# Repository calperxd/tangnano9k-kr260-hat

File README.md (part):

# Tang Nano 9K Custom HAT for AMD Kria KR260

Hardware, firmware, integration and validation requirements for a custom FPGA board based on the Tang Nano 9K, installed directly on the 40-pin J21 header of the KR260.

| Top | Bottom |
|:---:|:---:|
|  |  |

<p align="center"><sub>KiCad 3D renders of board revision 0.4 (65 × 56.5 mm, 4 layers). The board has not been manufactured yet.</sub></p>

| Field | Value |
|---|---|
| Document revision | 0.7 — TMI7003C checked against its datasheet; its LCSC number in the BOM |
| Date | 2026-10-21 |
| Previous revisions | 0.6 — power from the USB-C or from the KR260 J21 5 V (Schottky OR-ing); 0.5 — English translation, KR260 schematic cross-check, PCB prepared for JLCPCB; 0.4 — preliminary schematic and proposed parts; 0.3 — integration with the KR260; 0.2 — consolidation of the HAT scope (all dated 2026-10-21) |
| Host platform | AMD Kria KR260; K26 SOM with XCK26-SFVC784-2LV-C/I (F10) |
| KR260 environment | KAKUEI-OS (customized PetaLinux 2024.2), Vivado/Vitis 2024.2, PL with DPU (DPUCZDX8G) and VCU, applications in Docker containers (R4) |
| Status | Specification with a preliminary schematic and a PCB prepared for JLCPCB fabrication and assembly in KiCad 10 (`hardware/`, Proposed); production files generated for an order, not released; mechanical fit with the KR260 checked against its 3D model (XTP744, F14), with the physical fit check still **Pending**; pinout, outline and PCB still subject to development and validation |
| Planned CAD | KiCad 10 |
| Expansion board FPGA | Gowin GW1NR-LV9QN88PC6/I5, QN88P package |

> **This document is not a release for manufacturing.** The number of usable signals on J21, the clock pins, the voltages, the mechanical fit and the link timing need to be proven in the design. **16 bits at 50 MHz correspond to 100 MB/s raw by calculation, not to a rate already measured or guaranteed.**
>
> **Revision 0.3:** the J21 → K26 map comes from a secondary source and is **preliminary — confirm in XTP743**. The signal allocation on J21 is **Proposed**. Nothing in this revision was measured or validated in hardware.
>
> **Revision 0.4:** the preliminary schematic in `hardware/` was captured in KiCad 10. An ERC with no violations and a netlist checked against the intended connections are document checks, not electrical validation. The new parts are **Proposed** (section 16.1). After the capture, the five sheets were redrawn with wires, power symbols and labels, with no change in connectivity (section 17.1). There is also a PCB study with a provisional outline and automatic routing (section 17.2), which neither defines the mechanics nor is a release for manufacturing.
>
> **Revision 0.5:** the document was translated to English. The J21 → K26 map was cross-checked against the KR260 carrier schematic (cited as XTP743; F12) and the K26 SOM XDC (F13): the 28 signal contacts match with 0 differences, the section 6.4 items are answered except PUDC_B (ISO-14, still **Pending**), and the rails behind the J21 3.3 V and the bank 43/44 VCCO are identified (ISO-10); these are document cross-checks, not hardware validation. The PCB was prepared for JLCPCB fabrication and assembly (section 17.2): English KiCad texts and silkscreen with J21 pin labels, JLCPCB design rules and stackup (Proposed), and the USB pair rerouted on F.Cu without vias (in rev. 0.4: D+ on F.Cu and D− on In2.Cu with 3 vias, 16.0/20.0 mm); other rev. 0.4 values that changed are given next to the new ones in section 17.2. The PUYA P25Q32U Flash, not stocked at JLCPCB and with its datasheet still Pending, was replaced by the Winbond W25Q32JVZPIQ (Proposed; MSPI/boot compatibility with the GW1NR-9 **Pending**), and the Gerber/drill, BOM and CPL files were generated for a JLCPCB order (sections 16 and 17.2). The KR260 carrier 3D model (XTP744, F14) was then read: in the model, J130 and the holes H1/H2 land on J21 and its two header-side holes, so the outline, holes and J21 position move from Pending to Proposed, while the J21 pin 1 position (MEC-02) and a physical fit check stay **Pending** (section 4). The files are not a release: the physical fit check on a KR260, the human design review and the other open items of section 20 remain.
>
> **Revision 0.6:** by design decision (2026-10-21), the HAT runs from either source: its own USB-C or the KR260 J21 5 V (contacts 2 and 4). This replaces “exclusively USB-C” in SYS-05 and PWR-01. Each source reaches +5V through its own B5819W Schottky diode (D3 after the USB-C PTC; D4 after J21, with the 10 µF C14), so neither source can feed the other (ISO-01, section 8.1). The FT2232H becomes self-powered: VBUS reaches its PWRSAV# input through a 4.7k/10k divider (R10/R11), which holds it in suspend while no USB host is present (FT_000061 v2.10, table 3.3 and section 6.2), and its EEPROM must be programmed for self-powered operation with “suspend on DBUS7 low” (section 9). The schematic (ERC with 0 errors and 0 warnings; netlist compared by script with rev. 0.5, only the intended differences) and the PCB (DRC with schematic parity: 0 errors, 0 unconnected pads) were updated and the production files regenerated (sections 16 and 17). These are document checks, not hardware validation; the TMI7003C input range with the lower +5V and the PWR-04 budget against the 1.0 A of J21 are **Pending**.
>
> **Revision 0.7:** the TMI7003C was checked against its datasheet (Toll Microelectronic, TMI7003C V1.5, 2024-07). The 13 functional pins (VIN1–3, EN1–3, LX1–3, FB1–3 and the GND exposed pad) match the symbol taken from the 3674; pins 1, 4, 5, 12, 13, 15, 16 and 17 are NC in the datasheet and stay tied as on the 3674 (GND, and +5V on pin 16). Its 2.5 to 5.5 V input range (UVLO 2.3 V, OVP 6.0 V) covers +5V one Schottky drop below either source, which closes that rev. 0.6 item. The BOM now carries the TMI7003C LCSC number (C840566), so only the GW1NR-LV9QN88PC6/I5 needs JLCPCB Global Sourcing or consignment. This is a document check, not hardware validation.

## 1. Objective, origin and scope

Create a **new PCB with the FPGA soldered directly onto it**, preserving the selected set of Tang Nano 9K functions and adding a communication interface with the KR260 programmable logic through J21. This is not an adapter board for plugging in a ready-made Tang Nano 9K.

The HAT must be able to operate in two ways:

- **Installed on the KR260:** powered by the KR260 through J21 (5 V on contacts 2 and 4) or by its own USB-C (SYS-05), with FPGA ↔ FPGA communication enabled when needed.
- **Standalone:** powered and programmed over USB-C, without depending on the presence of the KR260 for its local functions.

The priority of the link is to achieve **the highest demonstrable sustained speed with electrical and timing margin**, without sacrificing data integrity or low latency. The ARM/Linux processor must not be responsible for sampling each word of the external bus.

### 1.1 Documentary basis and conventions

This consolidation uses the draft **“Placa custom Tang Nano 9K + Pmod: requisitos” (“Custom Tang Nano 9K + Pmod board: requirements”), dated 2026-10-20** (R1), and the later design decisions (R2, R3). The original draft described a different connector and a different link; its information must not be transplanted automatically to J21.

Revision 0.3 incorporates the KR260 integration survey of 2026-10-21 (R5), based on AMD documentation and community sources, and the system context (R4):

- facts from official AMD documentation (**F1–F11**, section 21.3) are entered as fact, with the source cited;
- data from secondary sources (**S1–S4**, section 21.4) appear as **preliminary — confirm in XTP743**, or in the indicated official document when the data does not come from the schematic;
- new allocations and solutions are entered as **Proposed**, and what is not confirmed remains **Pending**. No new item was marked as Decided.

The primary sources listed at the end must be consulted during implementation. Their citation in this README **does not mean that their PDFs, pinouts or constraints were revalidated in this consolidation**. In revision 0.3, the only check made was a transcription check: the pin names of the J21 → K26 map against the pinout file `xczu5evsfvc784pkg.txt` (section 6.3). In revision 0.4, the schematic capture used documents opened in this revision: the Tang Nano 9K 3674 schematic and interactive BOM, Gowin's UG803E, UG119E and DS117E, the FT2232H datasheet and the TI datasheets of the proposed parts (section 21.2). The new choices of revision 0.4 are **Proposed**. In revision 0.5, local copies of AMD files were read and entered as facts F12 to F14 (section 21.3): the KR260 carrier schematic (cited as XTP743), the K26 SOM XDC and the XTP744 carrier 3D model. The J21 → K26 map, the carrier parts on the J21 path, the J21 power rails and the mechanical fit were cross-checked against them (sections 4, 6.3, 6.4, 8.3 and 17.2) as document and model checks, without hardware measurements.

| Marking | Meaning |
|---|---|
| **Decided** | Explicit design choice or requirement expressed in the source draft |
| **Proposed** | Technical solution discussed or recommended detailing; still requires approval/validation |
| **Pending** | There is not enough evidence or no final choice |
| **Validation requirement** | Criterion to be demonstrated; not a statement that the hardware already meets it |

The isolation, protocol, test and release details below make up the **proposed technical baseline**. They make the discussed objectives verifiable, without representing circuits already implemented. In the new requirements of revision 0.3, the status appears in bold at the start of the text.

### 1.2 Out of scope for this revision

Do not include Pmods, board-to-board link cables, HDMI, a new PCIe interface, a USB bridge dedicated to the main data stream or an FPGA change. Electrical/functional compatibility with a conventional Raspberry Pi is not an acceptance criterion: **the target is the KR260**.

## 2. Consolidated decisions

| ID | Item | Baseline | Status |
|---|---|---|---|
| SYS-01 | Host | AMD Kria KR260, not a conventional Raspberry Pi | Decided |
| SYS-02 | Mounting | HAT-type board, plugged into the 40-pin J21 header | Decided; mechanics to be validated |
| SYS-03 | Pmods | No Pmod connector | Decided |
| SYS-04 | FPGA | Same GW1NR-LV9QN88PC6/I5 as the reference | Decided |
| SYS-05 | Power | 5 V from the USB-C or from the KR260 J21 (contacts 2 and 4), either one alone, through Schottky OR-ing (section 8.1); until rev. 0.5, exclusively USB-C | Decided (rev. 0.6) |
| SYS-06 | microSD/TF | Keep the slot and its functionality | Decided |
| SYS-07 | HDMI | Remove the connector and the circuits exclusive to this interface | Decided |
| SYS-08 | Communication with the KR260 | Available in hardware; optional use in firmware | Decided |
| SYS-09 | Priority | Maximum real communication speed compatible with this design | Decided |
| SYS-10 | Flash, PSRAM, clock, LEDs and buttons | Preserve the selected functions of the Tang Nano 9K | Baseline requirement |
| SYS-11 | Programming bridge | FT2232H replacing the BL702 | Proposed in the base draft |
| SYS-12 | RGB/SPI LCD interfaces | Do not include in the current baseline | Proposed, kept from the previous scope |
| SYS-13 | Original Tang GPIO headers | Not reproduced automatically; no commitment to keep all of them exposed | Pending, depending on need |
| SYS-14 | PCB layers | Four | Proposed |
| SYS-15 | Dimensions | Discussed reference of 65 × 56.5 mm | Proposed; checked against the XTP744 3D model in rev. 0.5 (F14), physical fit check pending |
| SYS-16 | Main interface | 16-bit parallel bus with clock and control | Proposed, conditional on the pinout and the timing |
| SYS-17 | Initial frequency | 50 MHz; investigate higher frequencies after validation | Proposed |
| SYS-18 | Direction of the main flow | Tang → KR260 as the starting point | Proposed; final duplex pending |

**Scope replacements:** the two previously requested Pmods, the connection to the KR260 Pmods 3/4 and the 60 × 40 mm size are no longer requirements of this version. No circuit exclusive to these connections should remain through automatic copying.

The expression “based on the Tang Nano 9K” **does not mean preserving all external interfaces of the commercial board**: HDMI is removed, LCDs are outside the proposed baseline, the USB implementation changes and the exposure of the GPIOs changes.

## 3. Proposed functional architecture

```text
                            USB-C
                         5 V + USB 2.0
                            |
             +--------------+------------------+
             |                                 |
   Protection / regulators                   FT2232H
   +5V: USB-C 5 V or J21 5 V            JTAG A / UART B
   (contacts 2 and 4), Schottky OR             |
      3V3 / 1V8 / 1V2                          |
             |                                 |
             |                     JTAG conversion 3V3 <-> 1V8
             |                                 |
             +------------+--------------------+
                          |
                     GW1NR-9
                +---------+----------+
                |         |          |
            SPI Flash   microSD   LEDs / buttons
                |
           Application logic
                |
           FIFO / parallel TX
                |
   Protection and isolation for unpowered states
   (buffer OE controlled by LINK_EN - proposed)
                |
       2x20 female header on the bottom side
                |
         KR260 J21 -> K26 PL
                |
       RX / verification / CDC FIFO
                |
             AXI-Stream
                |
        AXI DMA -> DDR -> software
```

The diagram is functional, not a netlist. Flash, microSD and controls are independent connections of the FPGA. The AXI DMA/DDR chain is an integration proposal and is not mandatory for a consumer that operates entirely in the PL.

In revision 0.3, it is proposed that `LINK_EN`, driven by the KR260 PL, enable the HAT drivers in hardware (ISO-11), and that the RX go into the same bitstream as the DPU and the VCU (KRIA-02).

## 4. Mechanical requirements

| ID | Requirement |
|---|---|
| MEC-01 | Use a 40-way, 2 × 20, 2.54 mm pitch female connector on the bottom side, aligned with the actual J21. |
| MEC-02 | Check the numbering and mirroring between symbol, footprint, bottom view and host connector. Rev. 0.5: the XTP744 model (F14) does not mark pin 1, so the J21 pin 1 position comes from S2 and remains **Pending** until a visual check on a real KR260 (see below). |
| MEC-03 | Confirm the outline, hole coordinates and header position in a mechanical drawing; do not infer these coordinates from the HAT name. Rev. 0.5: **Proposed** after a check against the XTP744 3D model (F14): J130 and the holes H1/H2 land on J21 and its two header-side holes (see below); a physical fit check is still pending. |
| MEC-04 | Validate the height of standoffs and connectors against the actual KR260 assembly, including heatsink, fan and nearby connectors. Rev. 0.5 (**Proposed**, from the model only): 8.5 mm J130 socket and 11 mm M2.5 standoffs, with the HAT bottom about 10.9 mm above the carrier; the nearest tall KR260 parts are listed below (F14). Validation on the actual assembly is still pending. |
| MEC-05 | Keep USB-C, microSD, buttons and test points usable with the HAT installed. Rev. 0.5: in the models, USB-C, microSD, both buttons, the JTAG header and the test points are on the part of the HAT that overhangs the carrier edge, so they stay reachable with the HAT installed (geometric statement, F14). |
| MEC-06 | Do not obstruct cooling or require disassembling the KR260 to insert/remove the card or the programming cable. |
| MEC-07 | Provide mechanical fastening and keepouts for screw heads/standoffs, without relying only on the friction of the header. Rev. 0.5 (**Proposed**): 11 mm M2.5 standoffs at H1 and H2, on the two KR260 holes next to J21 (F14); H3 and H4 fall outside the carrier and have no support (optional feet). |
| MEC-08 | Mark pin 1, mounting orientation, board name, revision and power on the silkscreen. |
| MEC-09 | Define the PCB thickness, number/diameter of holes and tolerances together with the manufacturer and the chosen connectors. |
| MEC-10 | **Proposed.** Use the carrier 3D CAD model (XTP744) as the source for the outline, holes and heights on the KR260 side, recording the revision of the downloaded package. Rev. 0.5: read as F14 (package readme v1.0, 2022; `KR260-startkit-A02.stp`, assembly KR260_STARTKIT_ASM of 2021-10-15, carrier 128_05101_01 rev A02). |
| MEC-11 | **Proposed** (rev. 0.5, F14; Pending in rev. 0.4). The HAT form factor assumes the Raspberry Pi mounting holes. The carrier 3D model has two 2.77 mm holes on the J21 centreline, 58.0 mm apart and 4.87 mm beyond the end pins: the two header-side holes of the Raspberry Pi HAT pattern. The carrier schematic shows two grounded mounting holes, MH11 and MH12, on the J21 sheet (F12, sheet 12); matching them to the model holes is an inference from the geometry, because the STEP has no reference designators. The HAT holes H1 and H2 land on the two model holes (see below), which is the basis for the fastening of MEC-07 and the outline of SYS-15, still subject to a physical fit check. |

**Dimensions not yet approved:** 65 × 56.5 mm (the Raspberry Pi HAT size) was the initial reference, not a measurement taken from an official drawing at this stage. Confirm the applicable mechanical specification and, above all, the fit on the KR260 before freezing the outline. In revision 0.5, the outline was checked against the KR260 3D model (F14, below); the physical fit on a KR260 is still to be confirmed.

**Kit envelope (F3):** with the active thermal solution (fan and heatsink), the KR260 kit measures 119 × 140 × 36 mm, according to the official product page. This is the external size of the kit; it does not give the position of J21 or the clearance above the nearby components, which must come from XTP744. Revision 0.5 takes them from XTP744 (F14, below).

**Fit on the KR260 3D model (F14, revision 0.5; model check, no hardware measured):** placed with its body hanging outward over the right edge of the carrier, the HAT maps as HAT (x, y) → carrier (125.94 + y, 38.31 + x) mm, so J130 pin 1 (8.37, 4.77) lands on the J21 outer column at (130.71, 46.68), and the holes H1 (3.5, 3.5) and H2 (61.5, 3.5) land on the two carrier holes at (129.44, 41.81) and (129.44, 99.81). The HAT covers only a 9.1 mm strip of the carrier, where the only KR260 part is J21 and the only HAT bottom-side part is J130; the other ~47 mm overhang the carrier edge. The nearest tall KR260 parts are the dual RJ45 (top 27.0 mm above the carrier) at 9.7 mm from the HAT outline, the SFP cage (10.2 mm) at 14.5 mm, the SOM fan heatsink (29.2 mm) at 40.8 mm and the dual USB (15.7 mm) at 47.3 mm. With the 8.5 mm J130 socket on the J21 plastic body (top at 2.40 mm), the HAT bottom is about 10.9 mm above the carrier, held by 11 mm M2.5 standoffs at H1 and H2 (**Proposed**); H3 and H4 fall outside the carrier and have no support (optional feet). The J21 pins stand 5.84 mm above their plastic body.

**Fit indication and orientation (S2 — preliminary):** the LogicTronix tutorial shows a Sense HAT mounted on J21. This indicates that a commercial HAT physically fits the header, but it does not validate the fastening, the clearances or the outline of this HAT. The 3D model (F14) does not mark pin 1, so the orientation still comes from this photo: the Sense HAT hangs off the right edge of the KR260, and with the HAT convention (HAT body on the odd-row side), J21 pin 1 is the outer column (x 130.71) at the end toward the Pmod connectors (y 46.69). A HAT facing inward would hit the SOM fan heatsink and the dual RJ45 (F14). The J21 pin 1 position remains **Pending** until a visual check on a real KR260 (MEC-02).

Deliverable for this stage: 3D model of the assembly or overlay drawing with all critical clearances dimensioned, using XTP744 as the carrier model. In revision 0.5, a KiCad 3D view of the HAT on the KR260 model exists; it is kept outside the repository because it shows the licensed model, and the clearances obtained from the model are listed above.

## 5. FPGA resources and compatibility with the Tang Nano 9K

### 5.1 Reference voltages and pins

The values below come from the provided draft and must be cross-checked with the datasheet/pinout of the **exact part number and package**.

| Domain | Design voltage in the base draft | Note |
|---|---|---|
| Core | 1.2 V | Size tolerance, ripple and current according to the manufacturer |
| VCCIO0/1/2 | 3.3 V | Candidates for the interface with J21; on the K26 side, the carrier ties the VCCO of banks 43 and 44 to PL_3V3, shown as 3.3 V/3 A (F12) |
| VCCIO3 | 1.8 V | Supply tied to the PSRAM embedded in the QN88P according to the base draft |

The base draft states a range of **1.71 to 1.89 V for VCCIO3** on the QN88P. This is a critical requirement to be confirmed in the Gowin document: **do not raise VCCIO3 to 3.3 V to accommodate the expansion connector**.

| Preserved resource | Pins stated in the base draft | Requirement |
|---|---|---|
| UART | 17, 18 | Preserve the signals and directions of the reference |
| 27 MHz clock reference | 52 | Preserve frequency and functional circuit |
| P25Q32U SPI Flash (W25Q32JVZPIQ proposed in rev. 0.5, section 16.1) | 59–62 | Preserve interface and programming compatibility |
| microSD/TF card | 36–39 | Preserve the interface mode of the reference Tang |
| Buttons | 3, 4 | Two user buttons, respecting the 1.8 V bank |
| JTAG | 5–8 | Validate TCK/TDI/TDO/TMS pin by pin |
| RECONFIG_N | 9 | Preserve reconfiguration functionality |
| LEDs | 10, 11, 13–16 | Six user LEDs with a compatible circuit |
| MODE1/MODE0 | 87, 88 | Preserve the straps and boot sequence of the reference |

The ranges in this table **do not replace a net map**. Publish the complete correspondence between signal name and pin number before generating the final schematic.

### 5.2 Preservation requirements

**FPGA-01:** keep the FPGA and the integrated PSRAM associated with the specified component; do not assume additional external PSRAM.

**FPGA-02:** keep the original pins of the preserved functions. A change must be documented and approved, with the impact on the firmware identified; do not change the pinout silently to make routing easier.

**FPGA-03:** preserve boot from Flash, volatile programming and JTAG recovery access, as supported by the chosen set.

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
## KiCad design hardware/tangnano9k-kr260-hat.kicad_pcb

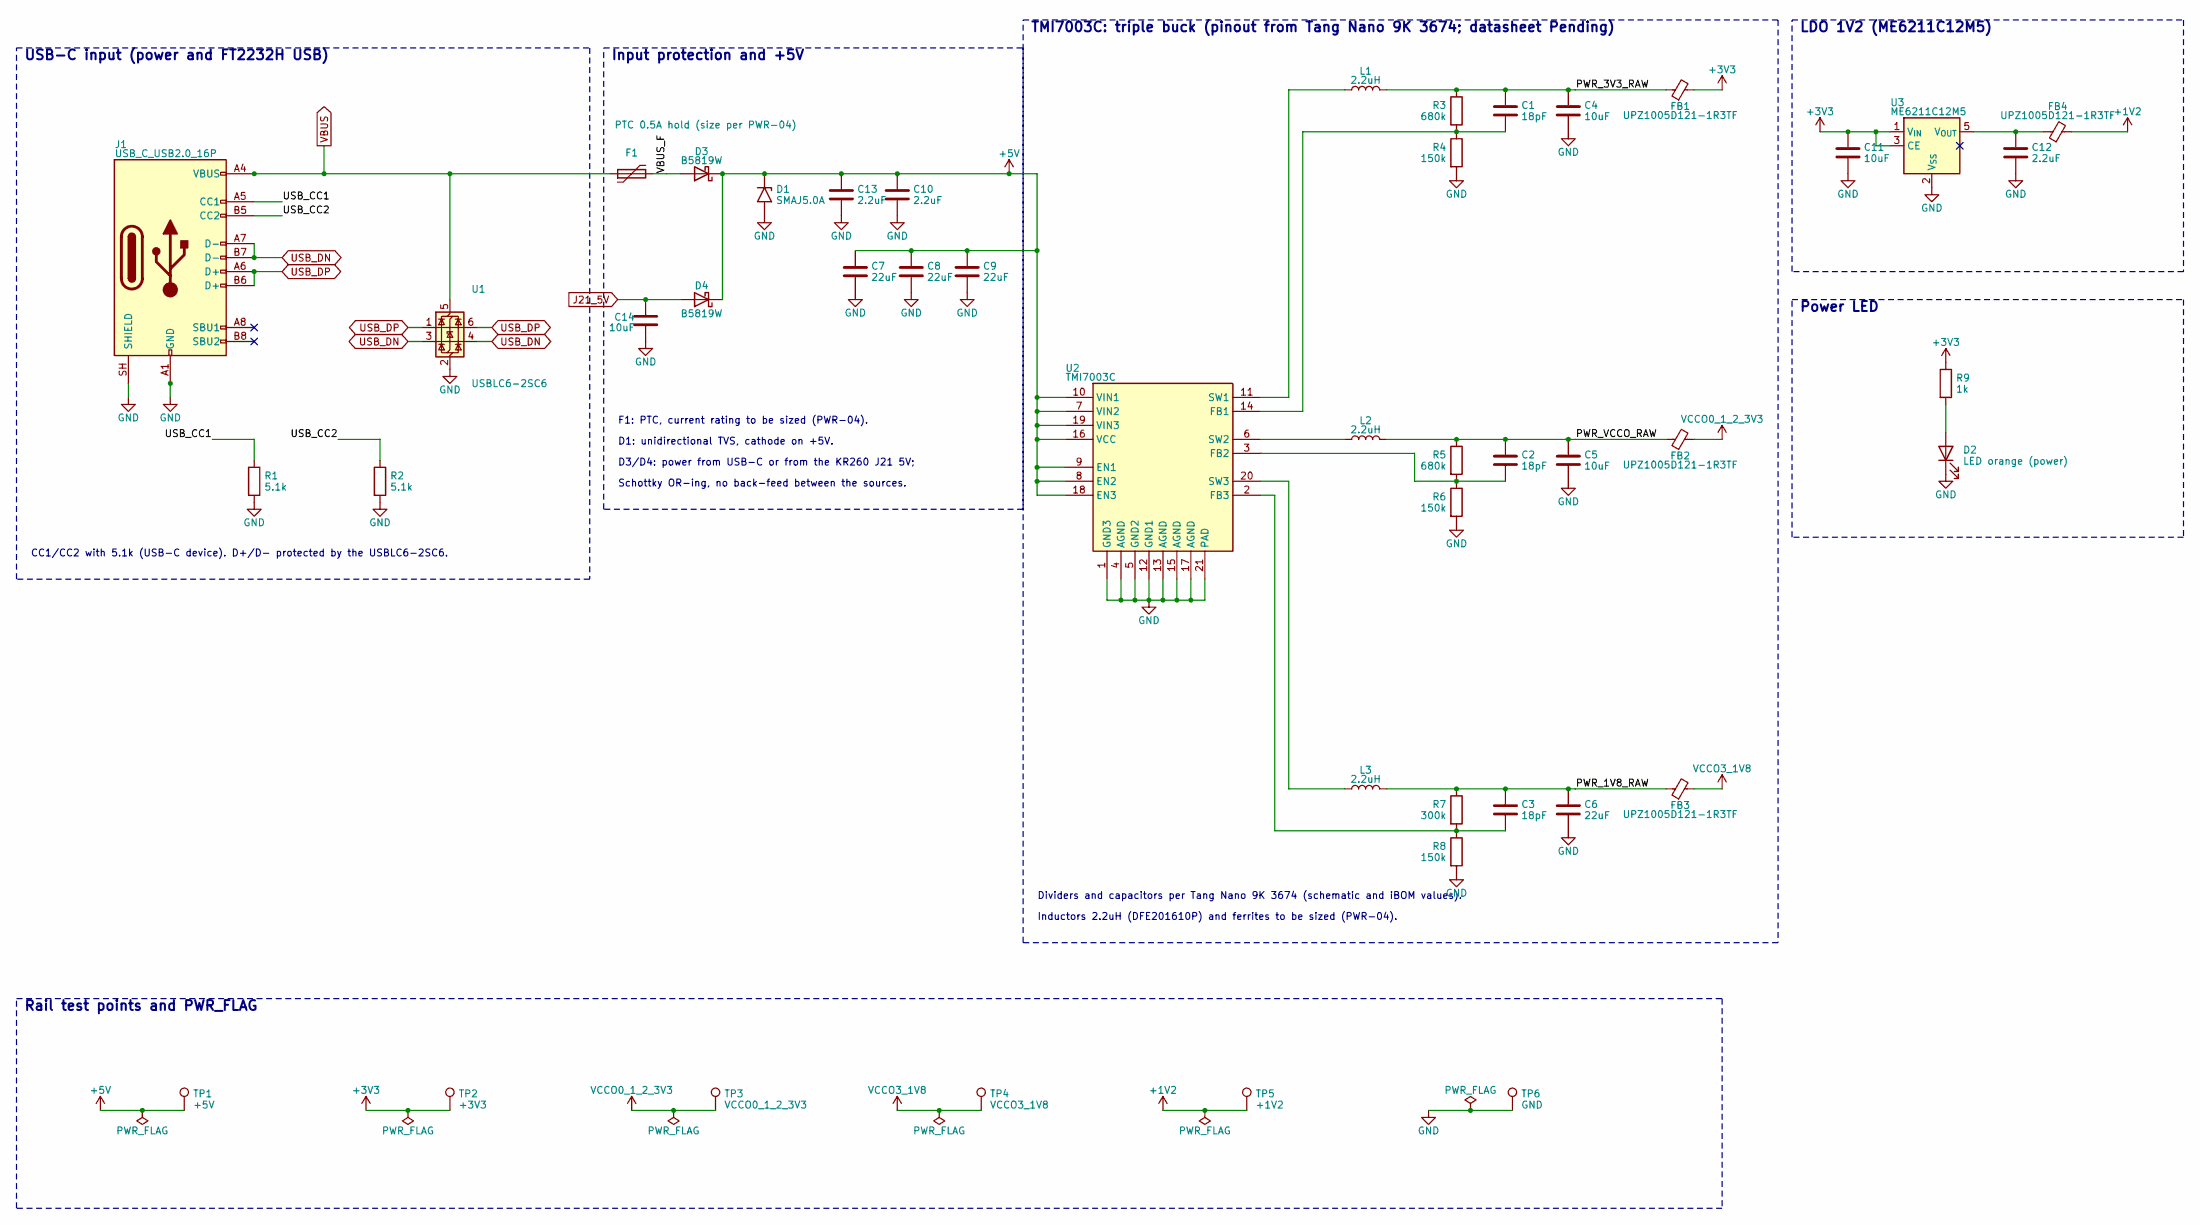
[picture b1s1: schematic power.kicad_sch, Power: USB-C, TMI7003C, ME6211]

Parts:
C1, C2, C3: 18pF; C_0402_1005Metric
C4, C5, C11, C14: 10uF; C_0603_1608Metric
C6, C7, C8, C9: 22uF; C_0603_1608Metric
C10, C12, C13: 2.2uF; C_0402_1005Metric
D1: SMAJ5.0A; D_SMA
D2: LED orange (power); LED_0603_1608Metric
D3, D4: B5819W; D_SOD-123
F1: PTC 0.5A hold (size per PWR-04); Fuse_1206_3216Metric
FB1, FB2, FB3, FB4: UPZ1005D121-1R3TF; L_0402_1005Metric
J1: USB_C_USB2.0_16P; USB_C_Receptacle_HRO_TYPE-C-31-M-12
L1, L2, L3: 2.2uH; L_Murata_DFE201610P
R1, R2: 5.1k; R_0402_1005Metric
R3, R5: 680k; R_0402_1005Metric
R4, R6, R8: 150k; R_0402_1005Metric
R7: 300k; R_0402_1005Metric
R9: 1k; R_0402_1005Metric
TP1: +5V; TestPoint_Pad_D1.0mm
TP2: +3V3; TestPoint_Pad_D1.0mm
TP3: VCCO0_1_2_3V3; TestPoint_Pad_D1.0mm
TP4: VCCO3_1V8; TestPoint_Pad_D1.0mm
TP5: +1V2; TestPoint_Pad_D1.0mm
TP6: GND; TestPoint_Pad_D1.0mm
U1: USBLC6-2SC6; SOT-23-6
U2: TMI7003C; QFN-20-1EP_3x3mm_P0.4mm_EP1.65x1.65mm
U3: ME6211C12M5; SOT-23-5

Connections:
+1V2: FB4.2, TP5.1; also elsewhere on the board
+3V3: C11.1, FB1.2, R9.1, TP2.1, U3.1 (V_{IN}), U3.3 (CE); also elsewhere on the board
+5V: C7.1, C8.1, C9.1, C10.1, C13.1, D1.1 (A1), D3.1 (K), D4.1 (K), TP1.1, U2.7 (VIN2), U2.8 (EN2), U2.9 (EN1), U2.10 (VIN1), U2.16 (VCC), U2.18 (EN3), U2.19 (VIN3)
/power/PWR_1V8_RAW: C3.1, C6.1, FB3.1, L3.2, R7.1
/power/PWR_3V3_RAW: C1.1, C4.1, FB1.1, L1.2, R3.1
/power/PWR_VCCO_RAW: C2.1, C5.1, FB2.1, L2.2, R5.1
/power/USB_CC1: J1.A5 (CC1), R1.1
/power/USB_CC2: J1.B5 (CC2), R2.1
/power/VBUS_F: D3.2 (A), F1.2
GND: C4.2, C5.2, C6.2, C7.2, C8.2, C9.2, C10.2, C11.2, C12.2, C13.2, C14.2, D1.2 (A2), D2.1 (K), J1.A1 (GND), J1.A12 (GND), J1.B1 (GND), J1.B12 (GND), J1.SH (SHIELD), R1.2, R2.2, R4.2, R6.2, R8.2, TP6.1, U1.2 (GND), U2.1 (GND3), U2.4 (AGND), U2.5 (GND2), U2.12 (GND1), U2.13 (AGND), U2.15 (AGND), U2.17 (AGND), U2.21 (PAD), U3.2 (V_{SS}); also elsewhere on the board
J21_5V: C14.1, D4.2 (A); also elsewhere on the board
unnamed: D2.2 (A), R9.2
unnamed: C1.2, R3.2, R4.1, U2.14 (FB1)
unnamed: C2.2, R5.2, R6.1, U2.3 (FB2)
unnamed: C3.2, R7.2, R8.1, U2.2 (FB3)
unnamed: L1.1, U2.11 (SW1)
unnamed: L2.1, U2.6 (SW2)
unnamed: L3.1, U2.20 (SW3)
unnamed: C12.1, FB4.1, U3.5 (V_{OUT})
USB_DN: J1.A7 (D-), J1.B7 (D-), U1.3 (I/O2), U1.4 (I/O2); also elsewhere on the board
USB_DP: J1.A6 (D+), J1.B6 (D+), U1.1 (I/O1), U1.6 (I/O1); also elsewhere on the board
VBUS: F1.1, J1.A4 (VBUS), J1.A9 (VBUS), J1.B4 (VBUS), J1.B9 (VBUS), U1.5 (VBUS); also elsewhere on the board
VCCO0_1_2_3V3: FB2.2, TP3.1; also elsewhere on the board
VCCO3_1V8: FB3.2, TP4.1; also elsewhere on the board

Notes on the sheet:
USB-C input (power and FT2232H USB)
CC1/CC2 with 5.1k (USB-C device). D+/D- protected by the USBLC6-2SC6.
Input protection and +5V
F1: PTC, current rating to be sized (PWR-04).
D1: unidirectional TVS, cathode on +5V.
D3/D4: power from USB-C or from the KR260 J21 5V;
Schottky OR-ing, no back-feed between the sources.
TMI7003C: triple buck (pinout from Tang Nano 9K 3674; datasheet Pending)
Dividers and capacitors per Tang Nano 9K 3674 (schematic and iBOM values).
Inductors 2.2uH (DFE201610P) and ferrites to be sized (PWR-04).
LDO 1V2 (ME6211C12M5)
Power LED
Rail test points and PWR_FLAG

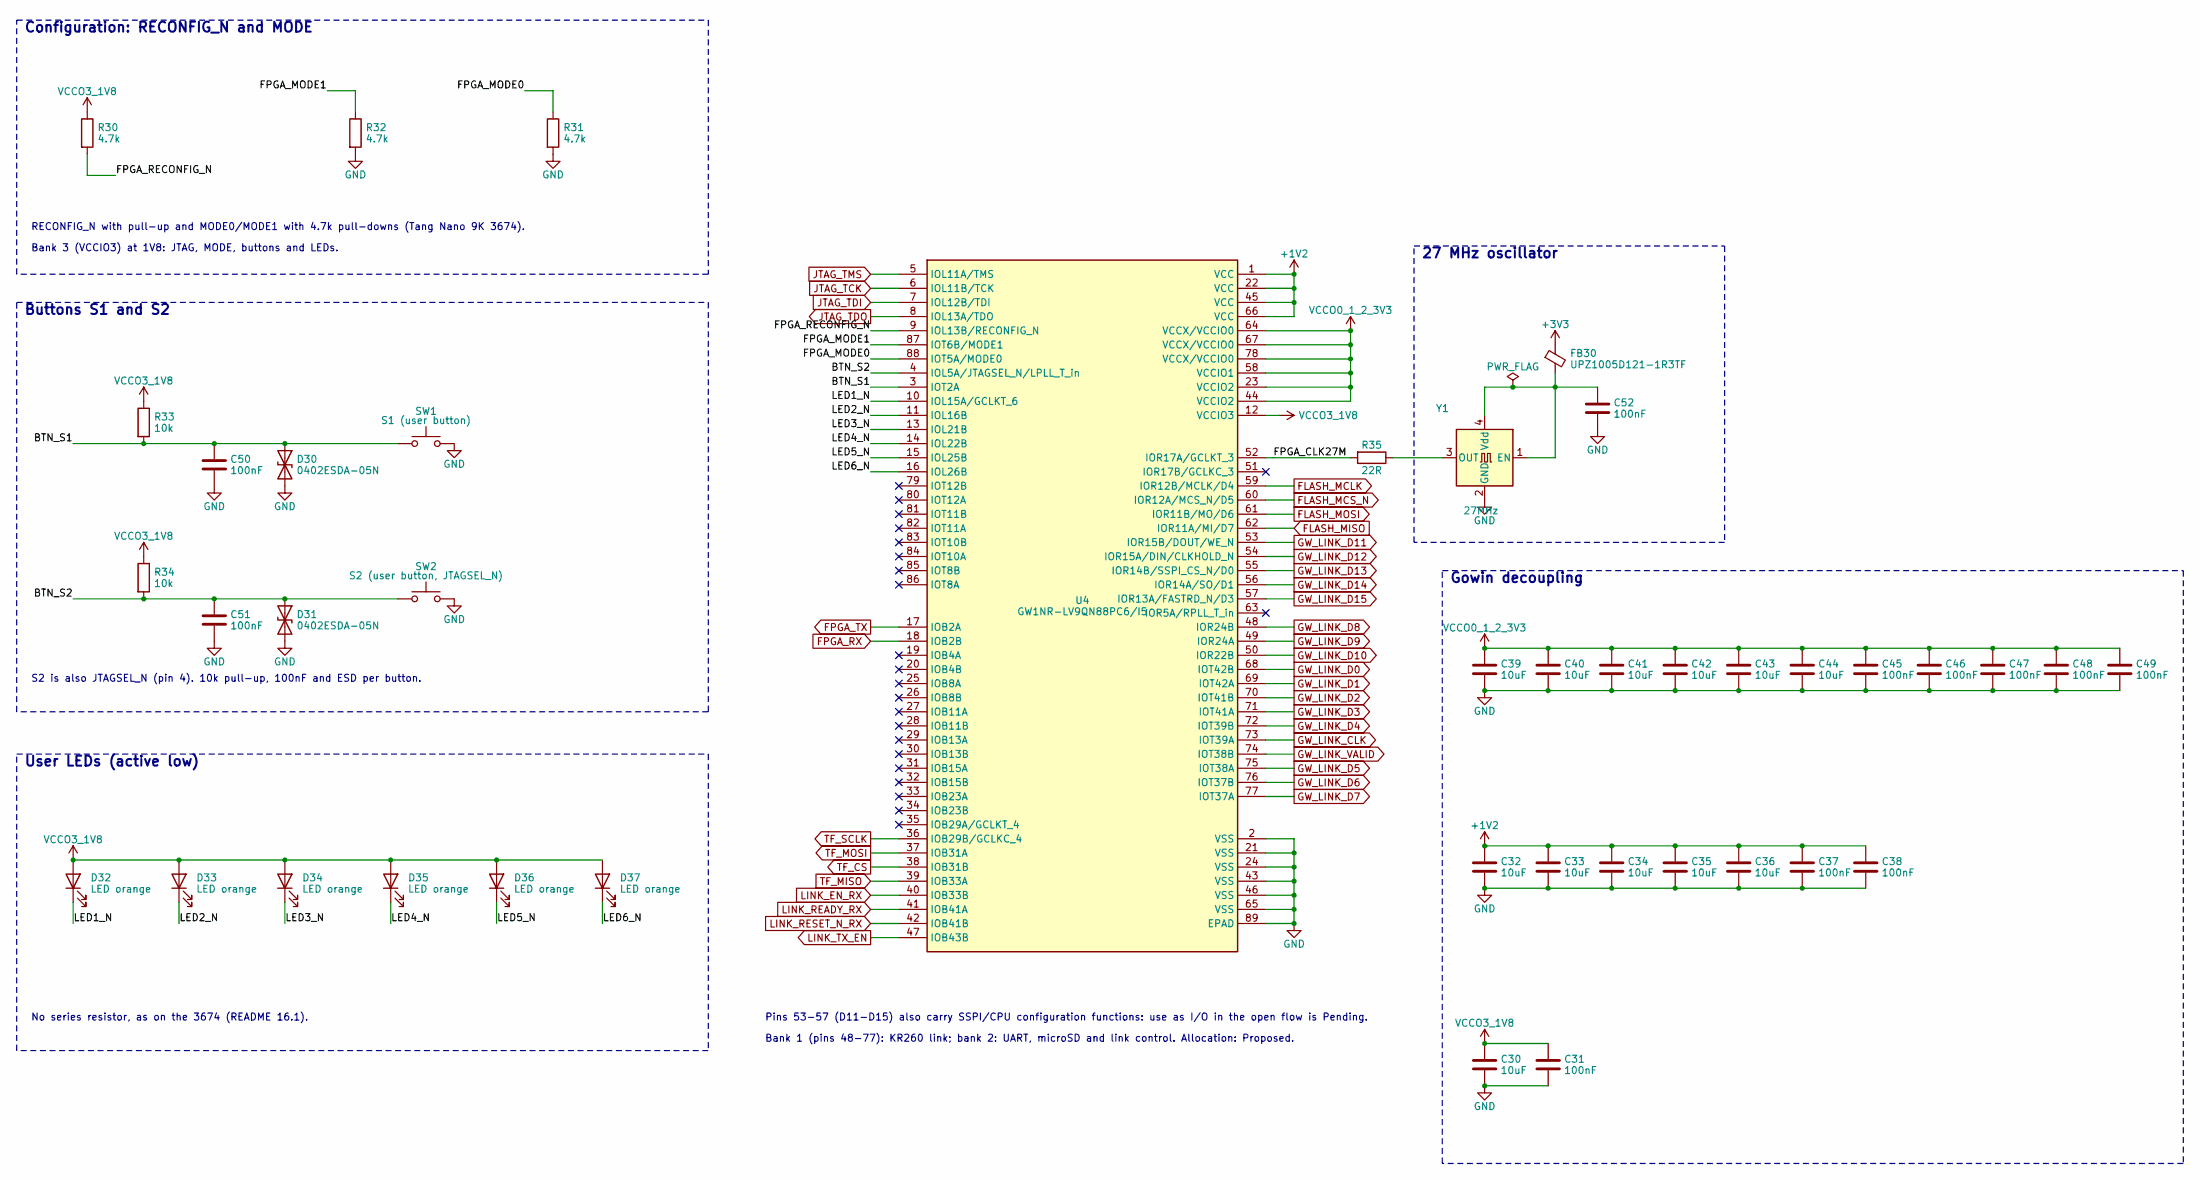
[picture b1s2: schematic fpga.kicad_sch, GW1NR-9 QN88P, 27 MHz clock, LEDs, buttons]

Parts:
C30, C32, C33, C34, C35, C36, C39, C40, C41, C42, C43, C44: 10uF; C_0603_1608Metric
C31, C37, C38, C45, C46, C47, C48, C49, C50, C51, C52: 100nF; C_0402_1005Metric
D30, D31: 0402ESDA-05N; D_0402_1005Metric
D32, D33, D34, D35, D36, D37: LED orange; LED_0603_1608Metric
FB30: UPZ1005D121-1R3TF; L_0402_1005Metric
R30, R31, R32: 4.7k; R_0402_1005Metric
R33, R34: 10k; R_0402_1005Metric
R35: 22R; R_0402_1005Metric
SW1: S1 (user button); SW_SPST_PTS810
SW2: S2 (user button, JTAGSEL_N); SW_SPST_PTS810
U4: GW1NR-LV9QN88PC6/I5; GW1NR_QN88P_10x10mm_P0.4mm_EP6.8mm
Y1: 27MHz; Oscillator_SMD_Abracon_ASE-4Pin_3.2x2.5mm

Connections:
+1V2: C32.1, C33.1, C34.1, C35.1, C36.1, C37.1, C38.1, U4.1 (VCC), U4.22 (VCC), U4.45 (VCC), U4.66 (VCC); also elsewhere on the board
+3V3: FB30.1; also elsewhere on the board
/fpga/BTN_S1: C50.1, D30.1 (A1), R33.2, SW1.1, U4.3 (IOT2A)
/fpga/BTN_S2: C51.1, D31.1 (A1), R34.2, SW2.1, U4.4 (IOL5A/JTAGSEL_N/LPLL_T_in)
/fpga/FPGA_CLK27M: R35.2, U4.52 (IOR17A/GCLKT_3)
/fpga/FPGA_MODE0: R31.1, U4.88 (IOT5A/MODE0)
/fpga/FPGA_MODE1: R32.1, U4.87 (IOT6B/MODE1)
/fpga/FPGA_RECONFIG_N: R30.2, U4.9 (IOL13B/RECONFIG_N)
/fpga/LED1_N: D32.1 (K), U4.10 (IOL15A/GCLKT_6)
/fpga/LED2_N: D33.1 (K), U4.11 (IOL16B)
/fpga/LED3_N: D34.1 (K), U4.13 (IOL21B)
/fpga/LED4_N: D35.1 (K), U4.14 (IOL22B)
/fpga/LED5_N: D36.1 (K), U4.15 (IOL25B)
/fpga/LED6_N: D37.1 (K), U4.16 (IOL26B)
FLASH_MCLK: U4.59 (IOR12B/MCLK/D4); also elsewhere on the board
FLASH_MCS_N: U4.60 (IOR12A/MCS_N/D5); also elsewhere on the board
FLASH_MISO: U4.62 (IOR11A/MI/D7); also elsewhere on the board
FLASH_MOSI: U4.61 (IOR11B/MO/D6); also elsewhere on the board
FPGA_RX: U4.18 (IOB2B); also elsewhere on the board
FPGA_TX: U4.17 (IOB2A); also elsewhere on the board
GND: C30.2, C31.2, C32.2, C33.2, C34.2, C35.2, C36.2, C37.2, C38.2, C39.2, C40.2, C41.2, C42.2, C43.2, C44.2, C45.2, C46.2, C47.2, C48.2, C49.2, C50.2, C51.2, C52.2, D30.2 (A2), D31.2 (A2), R31.2, R32.2, SW1.2, SW2.2, U4.2 (VSS), U4.21 (VSS), U4.24 (VSS), U4.43 (VSS), U4.46 (VSS), U4.65 (VSS), U4.89 (EPAD), Y1.2 (GND); also elsewhere on the board
GW_LINK_CLK: U4.73 (IOT39A); also elsewhere on the board
GW_LINK_D0: U4.68 (IOT42B); also elsewhere on the board
GW_LINK_D1: U4.69 (IOT42A); also elsewhere on the board
GW_LINK_D2: U4.70 (IOT41B); also elsewhere on the board
GW_LINK_D3: U4.71 (IOT41A); also elsewhere on the board
GW_LINK_D4: U4.72 (IOT39B); also elsewhere on the board
GW_LINK_D5: U4.75 (IOT38A); also elsewhere on the board
GW_LINK_D6: U4.76 (IOT37B); also elsewhere on the board
GW_LINK_D7: U4.77 (IOT37A); also elsewhere on the board
GW_LINK_D8: U4.48 (IOR24B); also elsewhere on the board
GW_LINK_D9: U4.49 (IOR24A); also elsewhere on the board
GW_LINK_D10: U4.50 (IOR22B); also elsewhere on the board
GW_LINK_D11: U4.53 (IOR15B/DOUT/WE_N); also elsewhere on the board
GW_LINK_D12: U4.54 (IOR15A/DIN/CLKHOLD_N); also elsewhere on the board
GW_LINK_D13: U4.55 (IOR14B/SSPI_CS_N/D0); also elsewhere on the board
GW_LINK_D14: U4.56 (IOR14A/SO/D1); also elsewhere on the board
GW_LINK_D15: U4.57 (IOR13A/FASTRD_N/D3); also elsewhere on the board
GW_LINK_VALID: U4.74 (IOT38B); also elsewhere on the board
JTAG_TCK: U4.6 (IOL11B/TCK); also elsewhere on the board
JTAG_TDI: U4.7 (IOL12B/TDI); also elsewhere on the board
JTAG_TDO: U4.8 (IOL13A/TDO); also elsewhere on the board
JTAG_TMS: U4.5 (IOL11A/TMS); also elsewhere on the board
LINK_EN_RX: U4.40 (IOB33B); also elsewhere on the board
LINK_READY_RX: U4.41 (IOB41A); also elsewhere on the board
LINK_RESET_N_RX: U4.42 (IOB41B); also elsewhere on the board
LINK_TX_EN: U4.47 (IOB43B); also elsewhere on the board
unnamed: C52.1, FB30.2, Y1.1 (EN), Y1.4 (Vdd)
unnamed: R35.1, Y1.3 (OUT)
TF_CS: U4.38 (IOB31B); also elsewhere on the board
TF_MISO: U4.39 (IOB33A); also elsewhere on the board
TF_MOSI: U4.37 (IOB31A); also elsewhere on the board
TF_SCLK: U4.36 (IOB29B/GCLKC_4); also elsewhere on the board
VCCO0_1_2_3V3: C39.1, C40.1, C41.1, C42.1, C43.1, C44.1, C45.1, C46.1, C47.1, C48.1, C49.1, U4.23 (VCCIO2), U4.44 (VCCIO2), U4.58 (VCCIO1), U4.64 (VCCX/VCCIO0), U4.67 (VCCX/VCCIO0), U4.78 (VCCX/VCCIO0); also elsewhere on the board
VCCO3_1V8: C30.1, C31.1, D32.2 (A), D33.2 (A), D34.2 (A), D35.2 (A), D36.2 (A), D37.2 (A), R30.1, R33.1, R34.1, U4.12 (VCCIO3); also elsewhere on the board

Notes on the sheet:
27 MHz oscillator
Configuration: RECONFIG_N and MODE
RECONFIG_N with pull-up and MODE0/MODE1 with 4.7k pull-downs (Tang Nano 9K 3674).
Bank 3 (VCCIO3) at 1V8: JTAG, MODE, buttons and LEDs.
Buttons S1 and S2
S2 is also JTAGSEL_N (pin 4). 10k pull-up, 100nF and ESD per button.
User LEDs (active low)
No series resistor, as on the 3674 (README 16.1).
Gowin decoupling
Pins 53-57 (D11-D15) also carry SSPI/CPU configuration functions: use as I/O in the open flow is Pending.
Bank 1 (pins 48-77): KR260 link; bank 2: UART, microSD and link control. Allocation: Proposed.

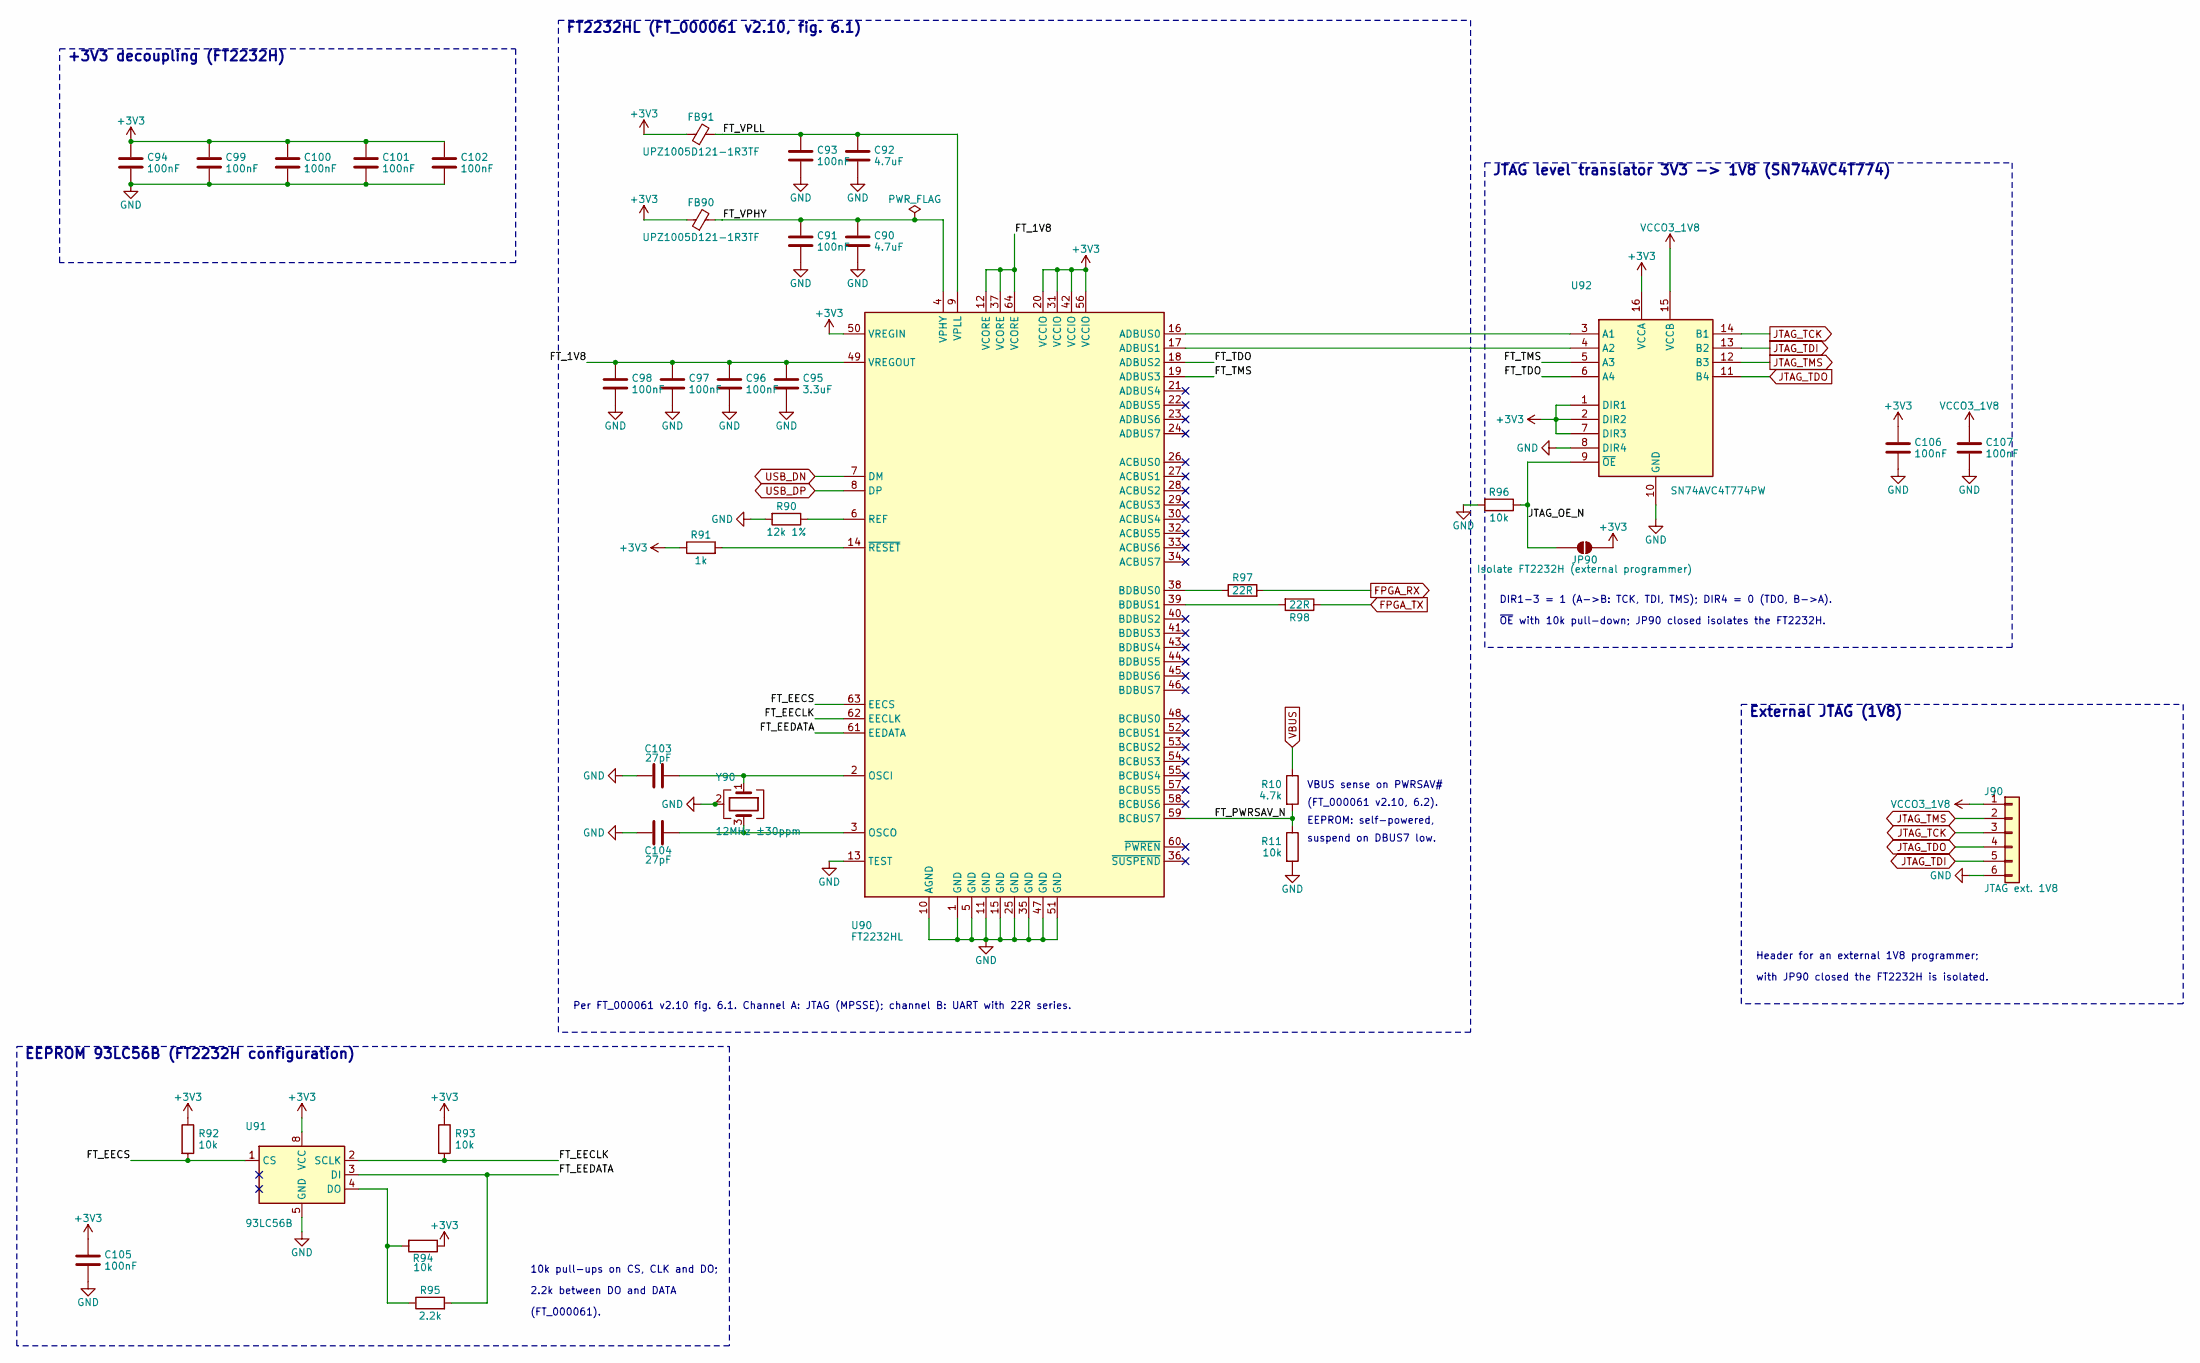
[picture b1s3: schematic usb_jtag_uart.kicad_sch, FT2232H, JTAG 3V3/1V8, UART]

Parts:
C90, C92: 4.7uF; C_0603_1608Metric
C91, C93, C94, C96, C97, C98, C99, C100, C101, C102, C105, C106, C107: 100nF; C_0402_1005Metric
C95: 3.3uF; C_0603_1608Metric
C103, C104: 27pF; C_0402_1005Metric
FB90, FB91: UPZ1005D121-1R3TF; L_0402_1005Metric
J90: JTAG ext. 1V8; PinHeader_1x06_P2.54mm_Vertical
JP90: Isolate FT2232H (external programmer); SolderJumper-2_P1.3mm_Open_RoundedPad1.0x1.5mm
R10: 4.7k; R_0402_1005Metric
R11, R92, R93, R94, R96: 10k; R_0402_1005Metric
R90: 12k 1%; R_0402_1005Metric
R91: 1k; R_0402_1005Metric
R95: 2.2k; R_0402_1005Metric
R97, R98: 22R; R_0402_1005Metric
U90: FT2232HL; LQFP-64_10x10mm_P0.5mm
U91: 93LC56B; SOIC-8_3.9x4.9mm_P1.27mm
U92: SN74AVC4T774PW; TSSOP-16_4.4x5mm_P0.65mm
Y90: 12MHz ±30ppm; Crystal_SMD_3225-4Pin_3.2x2.5mm

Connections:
+3V3: C94.1, C99.1, C100.1, C101.1, C102.1, C105.1, C106.1, FB90.1, FB91.1, JP90.2 (B), R91.1, R92.1, R93.1, R94.1, U90.20 (VCCIO), U90.31 (VCCIO), U90.42 (VCCIO), U90.50 (VREGIN), U90.56 (VCCIO), U91.8 (VCC), U92.1 (DIR1), U92.2 (DIR2), U92.7 (DIR3), U92.16 (VCCA); also elsewhere on the board
/usb_jtag_uart/FT_1V8: C95.1, C96.1, C97.1, C98.1, U90.12 (VCORE), U90.37 (VCORE), U90.49 (VREGOUT), U90.64 (VCORE)
/usb_jtag_uart/FT_EECLK: R93.2, U90.62 (EECLK), U91.2 (SCLK)
/usb_jtag_uart/FT_EECS: R92.2, U90.63 (EECS), U91.1 (CS)
/usb_jtag_uart/FT_EEDATA: R95.2, U90.61 (EEDATA), U91.3 (DI)
/usb_jtag_uart/FT_PWRSAV_N: R10.2, R11.1, U90.59 (BCBUS7)
/usb_jtag_uart/FT_TDO: U90.18 (ADBUS2), U92.6 (A4)
/usb_jtag_uart/FT_TMS: U90.19 (ADBUS3), U92.5 (A3)
/usb_jtag_uart/FT_VPHY: C90.1, C91.1, FB90.2, U90.4 (VPHY)
/usb_jtag_uart/FT_VPLL: C92.1, C93.1, FB91.2, U90.9 (VPLL)
/usb_jtag_uart/JTAG_OE_N: JP90.1 (A), R96.1, U92.9 (~OE)
FPGA_RX: R97.2; also elsewhere on the board
FPGA_TX: R98.1; also elsewhere on the board
GND: C90.2, C91.2, C92.2, C93.2, C94.2, C95.2, C96.2, C97.2, C98.2, C99.2, C100.2, C101.2, C102.2, C103.2, C104.2, C105.2, C106.2, C107.2, J90.6, R11.2, R90.2, R96.2, U90.1 (GND), U90.5 (GND), U90.10 (AGND), U90.11 (GND), U90.13 (TEST), U90.15 (GND), U90.25 (GND), U90.35 (GND), U90.47 (GND), U90.51 (GND), U91.5 (GND), U92.8 (DIR4), U92.10 (GND), Y90.2 (G), Y90.4 (G); also elsewhere on the board
JTAG_TCK: J90.3, U92.14 (B1); also elsewhere on the board
JTAG_TDI: J90.5, U92.13 (B2); also elsewhere on the board
JTAG_TDO: J90.4, U92.11 (B4); also elsewhere on the board
JTAG_TMS: J90.2, U92.12 (B3); also elsewhere on the board
unnamed: U90.16 (ADBUS0), U92.3 (A1)
unnamed: U90.17 (ADBUS1), U92.4 (A2)
unnamed: R97.1, U90.38 (BDBUS0)
unnamed: R98.2, U90.39 (BDBUS1)
unnamed: C103.1, U90.2 (OSCI), Y90.1
unnamed: C104.1, U90.3 (OSCO), Y90.3
unnamed: R90.1, U90.6 (REF)
unnamed: R91.2, U90.14 (~RESET)
unnamed: R94.2, R95.1, U91.4 (DO)
USB_DN: U90.7 (DM); also elsewhere on the board
USB_DP: U90.8 (DP); also elsewhere on the board
VBUS: R10.1; also elsewhere on the board
VCCO3_1V8: C107.1, J90.1, U92.15 (VCCB); also elsewhere on the board

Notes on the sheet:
FT2232HL (FT_000061 v2.10, fig. 6.1)
VBUS sense on PWRSAV#
(FT_000061 v2.10, 6.2).
EEPROM: self-powered,
suspend on DBUS7 low.
Per FT_000061 v2.10 fig. 6.1. Channel A: JTAG (MPSSE); channel B: UART with 22R series.
JTAG level translator 3V3 -> 1V8 (SN74AVC4T774)
DIR1-3 = 1 (A->B: TCK, TDI, TMS); DIR4 = 0 (TDO, B->A).
~{OE} with 10k pull-down; JP90 closed isolates the FT2232H.
EEPROM 93LC56B (FT2232H configuration)
10k pull-ups on CS, CLK and DO;
2.2k between DO and DATA
(FT_000061).
+3V3 decoupling (FT2232H)
External JTAG (1V8)
Header for an external 1V8 programmer;
with JP90 closed the FT2232H is isolated.

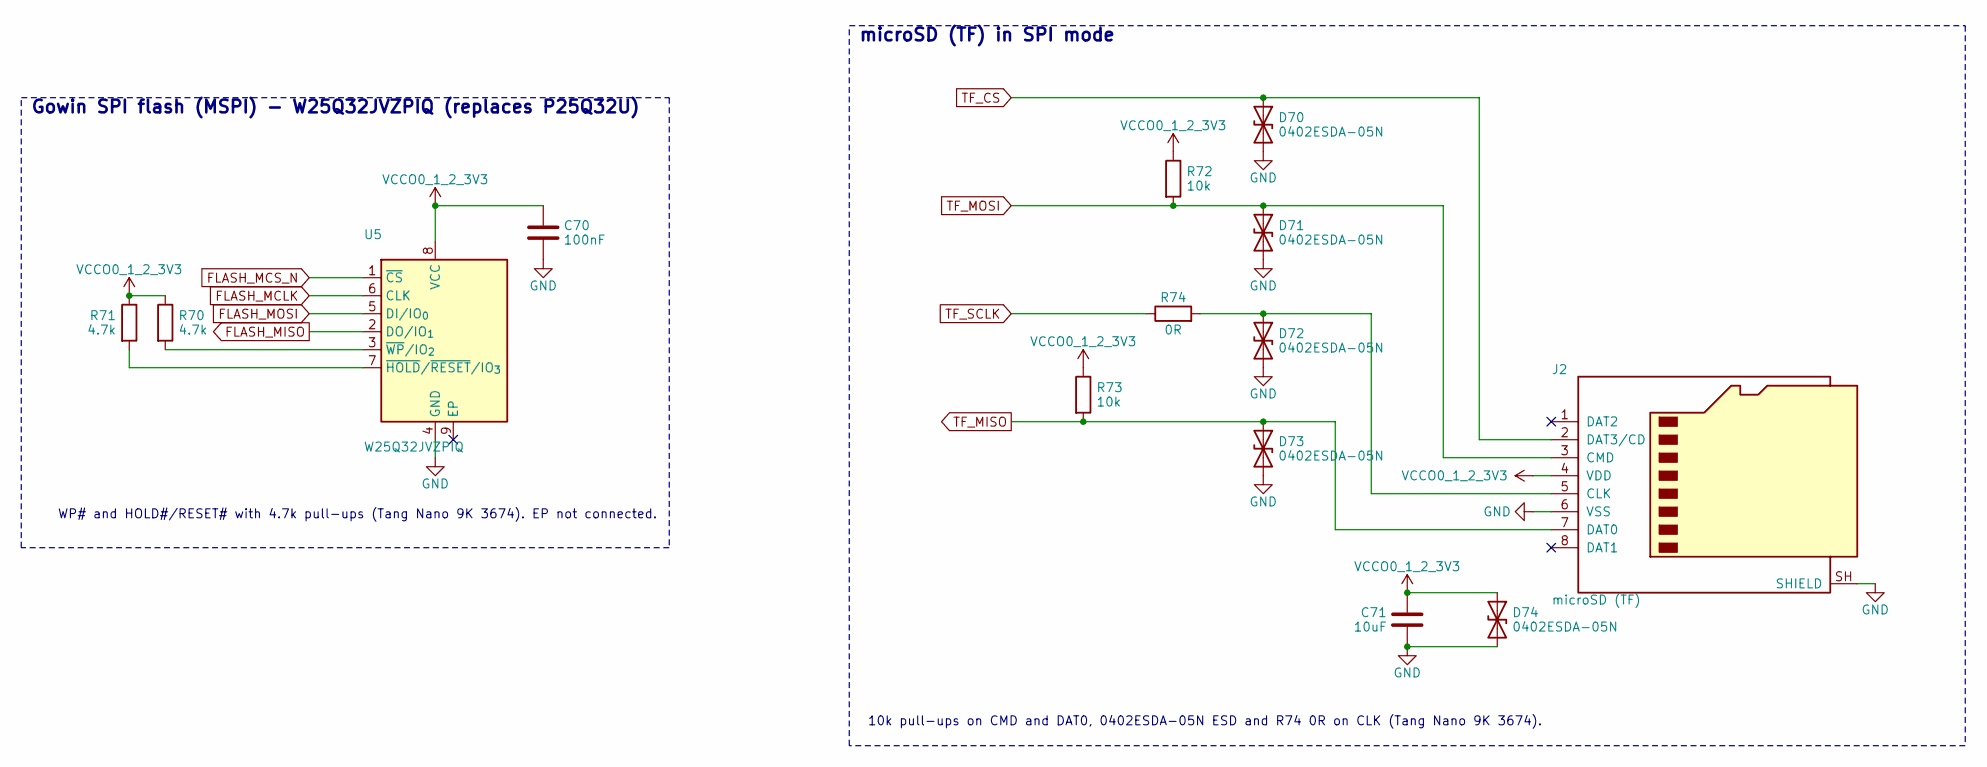
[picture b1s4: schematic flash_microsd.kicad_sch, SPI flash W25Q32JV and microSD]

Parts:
C70: 100nF; C_0402_1005Metric
C71: 10uF; C_0603_1608Metric
D70, D71, D72, D73, D74: 0402ESDA-05N; D_0402_1005Metric
J2: microSD (TF); microSD_HC_Molex_104031-0811
R70, R71: 4.7k; R_0402_1005Metric
R72, R73: 10k; R_0402_1005Metric
R74: 0R; R_0402_1005Metric
U5: W25Q32JVZPIQ; WSON-8-1EP_6x5mm_P1.27mm_EP3.4x4mm

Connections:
FLASH_MCLK: U5.6 (CLK); also elsewhere on the board
FLASH_MCS_N: U5.1 (~CS); also elsewhere on the board
FLASH_MISO: U5.2 (DO/IO_{1}); also elsewhere on the board
FLASH_MOSI: U5.5 (DI/IO_{0}); also elsewhere on the board
GND: C70.2, C71.2, D70.2 (A2), D71.2 (A2), D72.2 (A2), D73.2 (A2), D74.2 (A2), J2.6 (VSS), J2.SH (SHIELD), U5.4 (GND); also elsewhere on the board
unnamed: D72.1 (A1), J2.5 (CLK), R74.2
unnamed: R71.2, U5.7 (~HOLD/~RESET/IO_{3})
unnamed: R70.2, U5.3 (~WP/IO_{2})
TF_CS: D70.1 (A1), J2.2 (DAT3/CD); also elsewhere on the board
TF_MISO: D73.1 (A1), J2.7 (DAT0), R73.2; also elsewhere on the board
TF_MOSI: D71.1 (A1), J2.3 (CMD), R72.2; also elsewhere on the board
TF_SCLK: R74.1; also elsewhere on the board
VCCO0_1_2_3V3: C70.1, C71.1, D74.1 (A1), J2.4 (VDD), R70.1, R71.1, R72.1, R73.1, U5.8 (VCC); also elsewhere on the board

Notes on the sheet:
Gowin SPI flash (MSPI) - W25Q32JVZPIQ (replaces P25Q32U)
WP# and HOLD#/RESET# with 4.7k pull-ups (Tang Nano 9K 3674). EP not connected.
microSD (TF) in SPI mode
10k pull-ups on CMD and DAT0, 0402ESDA-05N ESD and R74 0R on CLK (Tang Nano 9K 3674).

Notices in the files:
README.md:
Copyright © 2026 Gabriel Calper. All rights reserved. The design is published for portfolio and reference purposes; no license is granted to copy, modify or manufacture it. See [LICENSE](LICENSE).
